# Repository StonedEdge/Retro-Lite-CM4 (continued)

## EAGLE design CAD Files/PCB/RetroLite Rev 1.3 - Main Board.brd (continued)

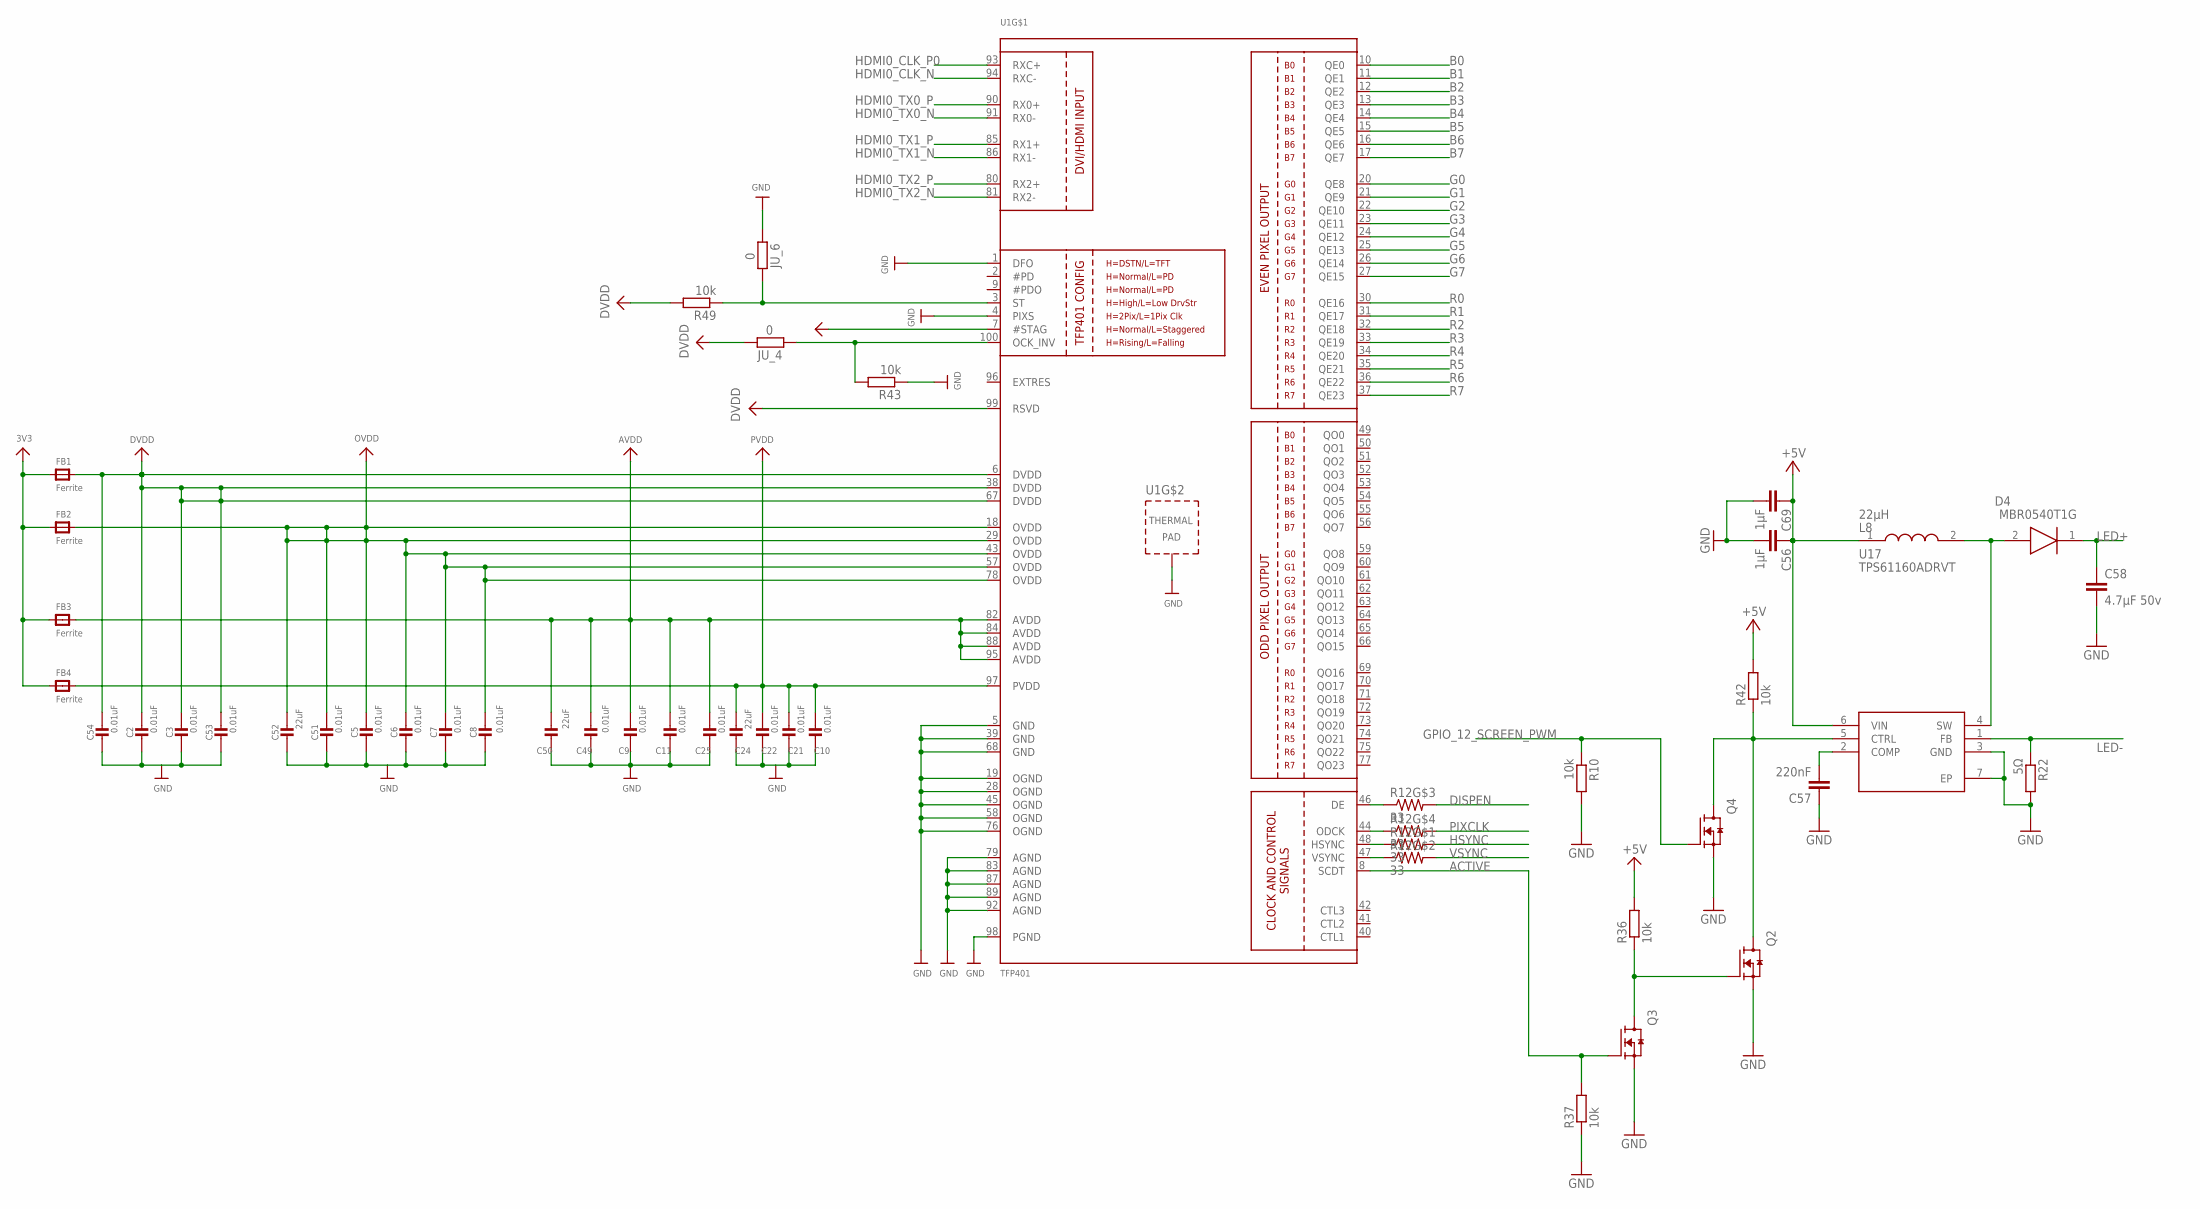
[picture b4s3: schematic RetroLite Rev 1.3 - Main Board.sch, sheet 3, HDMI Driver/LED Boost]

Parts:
C2, C3, C5, C6, C7, C8, C9, C10, C11, C21, C22, C25, C49, C51, C53, C54: 0.01uF; 0603-NO
C24, C50, C52: 22uF; 0603-NO
C56, C69: 1µF; C0603
C57: 220nF; C0603
C58: 4.7µF 50v; C0805
D4: MBR0540T1G; SOD3716X135N
FB1, FB2, FB3, FB4: Ferrite; _0805MP
JU_4, JU_6: 0; R0402
L8: 22µH; VLCF4020_1
Q2, Q3, Q4: AO3400A; SOT95P280X125-3N
R10, R36, R37, R42: 10k; R0603
R12: 33; RESPACK_4X0603
R22: 5Ω; R0603
R43, R49: 10k; R0402
U1: TFP401; S-PQFP-G100
U17: TPS61160ADRVT; SON65P200X200X80-7N

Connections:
3V3: FB1.1, FB2.1, FB3.1, FB4.1; also elsewhere on the board
+5V: C56.1, C69.1, L8.1, R36.2, R42.2, U17.6 (VIN); also elsewhere on the board
ACTIVE: Q3.1 (G), R37.2, U1.8 (SCDT); also elsewhere on the board
ASD: R12.3 (1), U1.46 (DE)
AVDD: C9.1, C11.1, C25.1, C49.1, C50.1, FB3.2, U1.82 (AVDD), U1.84 (AVDD), U1.88 (AVDD), U1.95 (AVDD)
B0: U1.10 (QE0); also elsewhere on the board
B1: U1.11 (QE1); also elsewhere on the board
B2: U1.12 (QE2); also elsewhere on the board
B3: U1.13 (QE3); also elsewhere on the board
B4: U1.14 (QE4); also elsewhere on the board
B5: U1.15 (QE5); also elsewhere on the board
B6: U1.16 (QE6); also elsewhere on the board
B7: U1.17 (QE7); also elsewhere on the board
CVB: R12.2 (1), U1.47 (VSYNC)
DISPEN: R12.6 (2); also elsewhere on the board
DVDD: C2.1, C3.1, C53.1, C54.1, FB1.2, JU_4.2, R49.2, U1.6 (DVDD), U1.7 (#STAG), U1.38 (DVDD), U1.67 (DVDD), U1.99 (RSVD)
G0: U1.20 (QE8); also elsewhere on the board
G1: U1.21 (QE9); also elsewhere on the board
G2: U1.22 (QE10); also elsewhere on the board
G3: U1.23 (QE11); also elsewhere on the board
G4: U1.24 (QE12); also elsewhere on the board
G5: U1.25 (QE13); also elsewhere on the board
G6: U1.26 (QE14); also elsewhere on the board
G7: U1.27 (QE15); also elsewhere on the board
GND: C2.2, C3.2, C5.2, C6.2, C7.2, C8.2, C9.2, C10.2, C11.2, C21.2, C22.2, C24.2, C25.2, C49.2, C50.2, C51.2, C52.2, C53.2, C54.2, C56.2, C57.1, C58.2, C69.2, JU_6.1, Q2.2 (S), Q3.2 (S), Q4.2 (S), R10.2, R22.2, R37.1, R43.1, U1.1 (DFO), U1.4 (PIXS), U1.5 (GND), U1.19 (OGND), U1.28 (OGND), U1.39 (GND), U1.45 (OGND), U1.58 (OGND), U1.68 (GND), U1.76 (OGND), U1.79 (AGND), U1.83 (AGND), U1.87 (AGND), U1.89 (AGND), U1.92 (AGND), U1.98 (PGND), U1.P$1 (TP), U1.P$2 (TP), U1.P$3 (TP), U1.P$4 (TP), U1.P$5 (TP), U1.P$6 (TP), U1.P$7 (TP), U1.P$8 (TP), U1.P$9 (TP), U1.P$10 (TP), U1.P$11 (TP), U1.P$12 (TP), U1.P$13 (TP), U1.P$14 (TP), U1.P$15 (TP), U1.P$16 (TP), U1.THERMAL (TP), U17.3 (GND), U17.7 (EP); also elsewhere on the board
GPIO_12_SCREEN_PWM: Q4.1 (G), R10.1; also elsewhere on the board
HDMI0_CLK_N: U1.94 (RXC-); also elsewhere on the board
HDMI0_CLK_P0: U1.93 (RXC+); also elsewhere on the board
HDMI0_TX0_N: U1.91 (RX0-); also elsewhere on the board
HDMI0_TX0_P: U1.90 (RX0+); also elsewhere on the board
HDMI0_TX1_N: U1.86 (RX1-); also elsewhere on the board
HDMI0_TX1_P: U1.85 (RX1+); also elsewhere on the board
HDMI0_TX2_N: U1.81 (RX2-); also elsewhere on the board
HDMI0_TX2_P: U1.80 (RX2+); also elsewhere on the board
HSYNC: R12.8 (2); also elsewhere on the board
LED+: C58.1, D4.1 (K); also elsewhere on the board
LED-: R22.1, U17.1 (FB); also elsewhere on the board
unnamed: C57.2, U17.2 (COMP)
unnamed: D4.2 (A), L8.2, U17.4 (SW)
unnamed: JU_4.1, R43.2, U1.100 (OCK_INV)
unnamed: Q2.3 (D), Q4.3 (D), R42.1, U17.5 (CTRL)
unnamed: Q2.1 (G), Q3.3 (D), R36.1
NEW: JU_6.2, R49.1, U1.3 (ST)
OVDD: C5.1, C6.1, C7.1, C8.1, C51.1, C52.1, FB2.2, U1.18 (OVDD), U1.29 (OVDD), U1.43 (OVDD), U1.57 (OVDD), U1.78 (OVDD)
PIXCLK: R12.5 (2); also elsewhere on the board
PVDD: C10.1, C21.1, C22.1, C24.1, FB4.2, U1.97 (PVDD)
R0: U1.30 (QE16); also elsewhere on the board
R1: U1.31 (QE17); also elsewhere on the board
R2: U1.32 (QE18); also elsewhere on the board
R3: U1.33 (QE19); also elsewhere on the board
R4: U1.34 (QE20); also elsewhere on the board
R5: U1.35 (QE21); also elsewhere on the board
R6: U1.36 (QE22); also elsewhere on the board
R7: U1.37 (QE23); also elsewhere on the board
VSYNC: R12.7 (2); also elsewhere on the board
XCV: R12.1, U1.48 (HSYNC)
ZXC: R12.4 (1), U1.44 (ODCK)

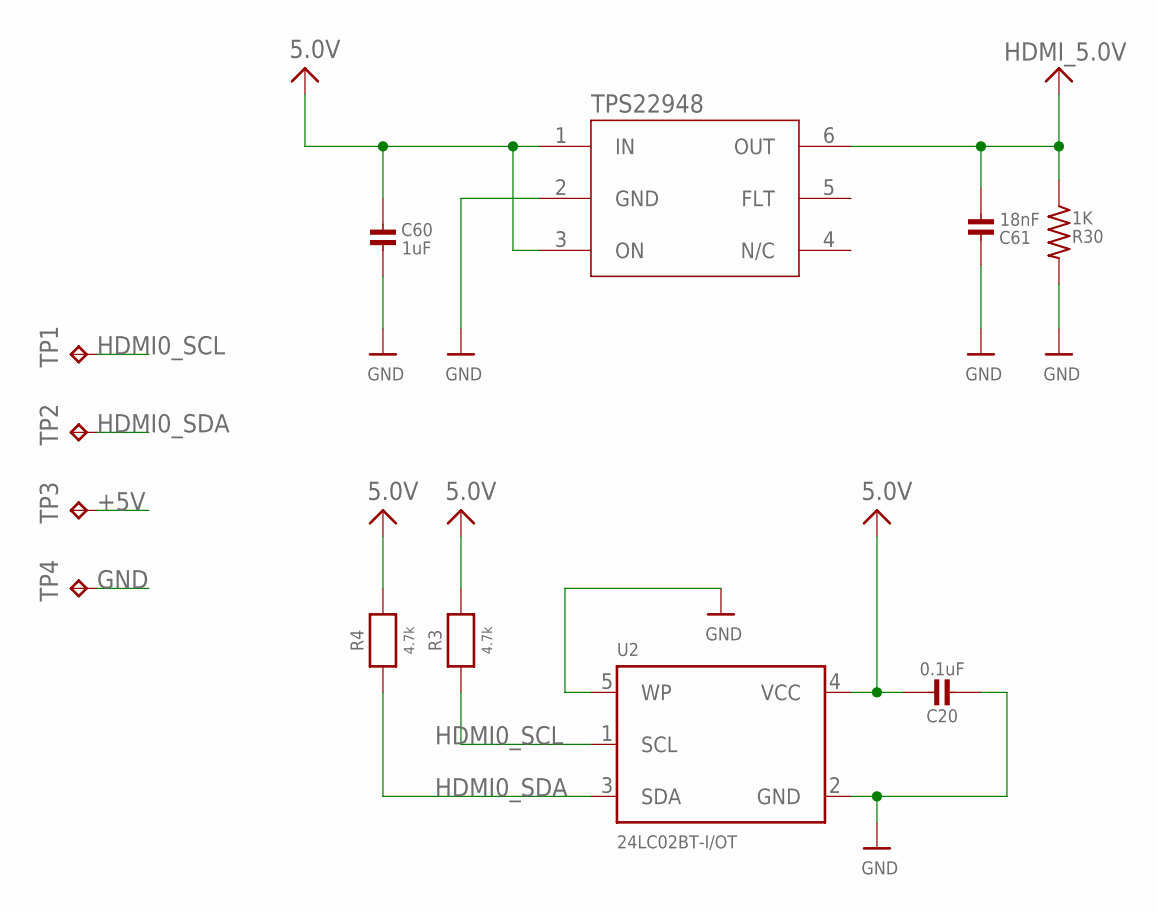
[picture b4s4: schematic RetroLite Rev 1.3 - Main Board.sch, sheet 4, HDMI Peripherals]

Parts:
C20: 0.1uF; 0603-NO
C60: 1uF; 0603-NO
C61: 18nF; 0603-NO
R3, R4: 4.7k; 0603-NO
R30: 1K; R0603
TP1, TP2, TP3, TP4: TPTP07R; TP07R
U2: 24LC02BT-I/OT; SOT23-5
U15: TPS22948; SOT65P210X110-6N

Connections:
+5V: C20.1, C60.1, R3.2, R4.2, TP3.TP, U2.4 (VCC), U15.1 (IN), U15.3 (ON); also elsewhere on the board
GND: C20.2, C60.2, C61.2, R30.2, TP4.TP, U2.2 (GND), U2.5 (WP), U15.2 (GND); also elsewhere on the board
HDMI0_SCL: R3.1, TP1.TP, U2.1 (SCL); also elsewhere on the board
HDMI0_SDA: R4.1, TP2.TP, U2.3 (SDA); also elsewhere on the board
HDMI_5.0V: C61.1, R30.1, U15.6 (OUT); also elsewhere on the board

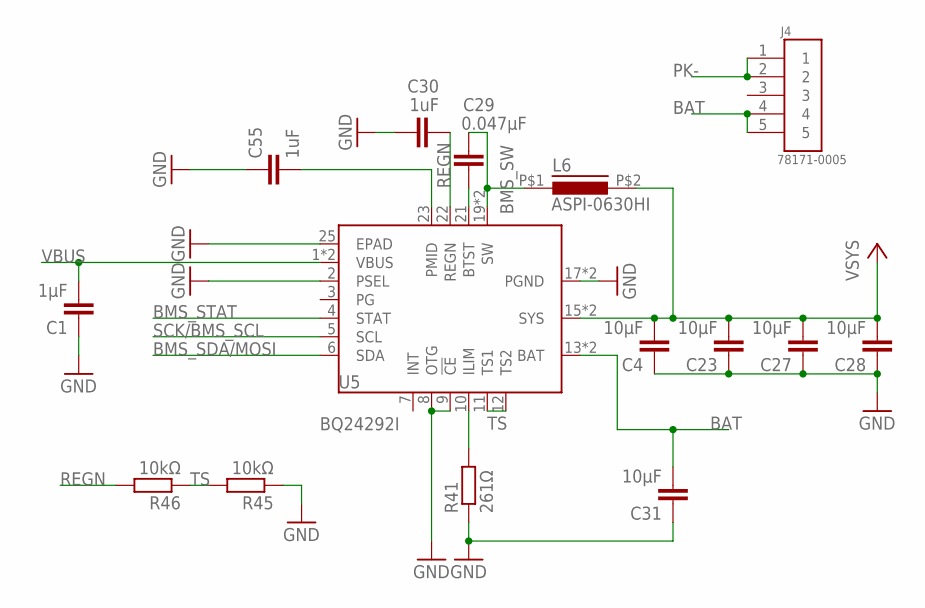
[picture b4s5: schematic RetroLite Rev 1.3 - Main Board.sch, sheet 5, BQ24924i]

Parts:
C1: 1µF; C0805
C4, C23, C27, C28, C31: 10µF; C0805
C29: 0.047µF; C0603
C30, C55: 1uF; C0603
J4: 78171-0005; MOLEX_78171-0005
L6: ASPI-0630HI
R41: 261Ω; R0603
R45, R46: 10kΩ; R0603
U5: BQ24292I; QFN50P400X400X100-25N

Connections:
BAT: C31.2, J4.4, J4.5, U5.13 (BAT), U5.14 (BAT); also elsewhere on the board
BMS_SDA/MOSI: U5.6 (SDA); also elsewhere on the board
BMS_STAT: U5.4 (STAT); also elsewhere on the board
BMS_SW: C29.1, L6.P$1 (1), U5.19 (SW), U5.20 (SW)
GND: C1.1, C4.1, C23.1, C27.1, C28.1, C30.1, C31.1, C55.1, R41.1, R45.1, U5.2 (PSEL), U5.8 (OTG), U5.9 (!CE), U5.17 (PGND), U5.18 (PGND), U5.25 (EPAD); also elsewhere on the board
unnamed: C55.2, U5.23 (PMID)
unnamed: C29.2, U5.21 (BTST)
unnamed: R41.2, U5.10 (ILIM)
PK-: J4.1, J4.2; also elsewhere on the board
REGN: C30.2, R46.2, U5.22 (REGN)
SCK/BMS_SCL: U5.5 (SCL); also elsewhere on the board
TS: R45.2, R46.1, U5.11 (TS1), U5.12 (TS2)
VBUS: C1.2, U5.1 (VBUS), U5.24 (VBUS); also elsewhere on the board
VSYS: C4.2, C23.2, C27.2, C28.2, L6.P$2 (2), U5.15 (SYS), U5.16 (SYS); also elsewhere on the board

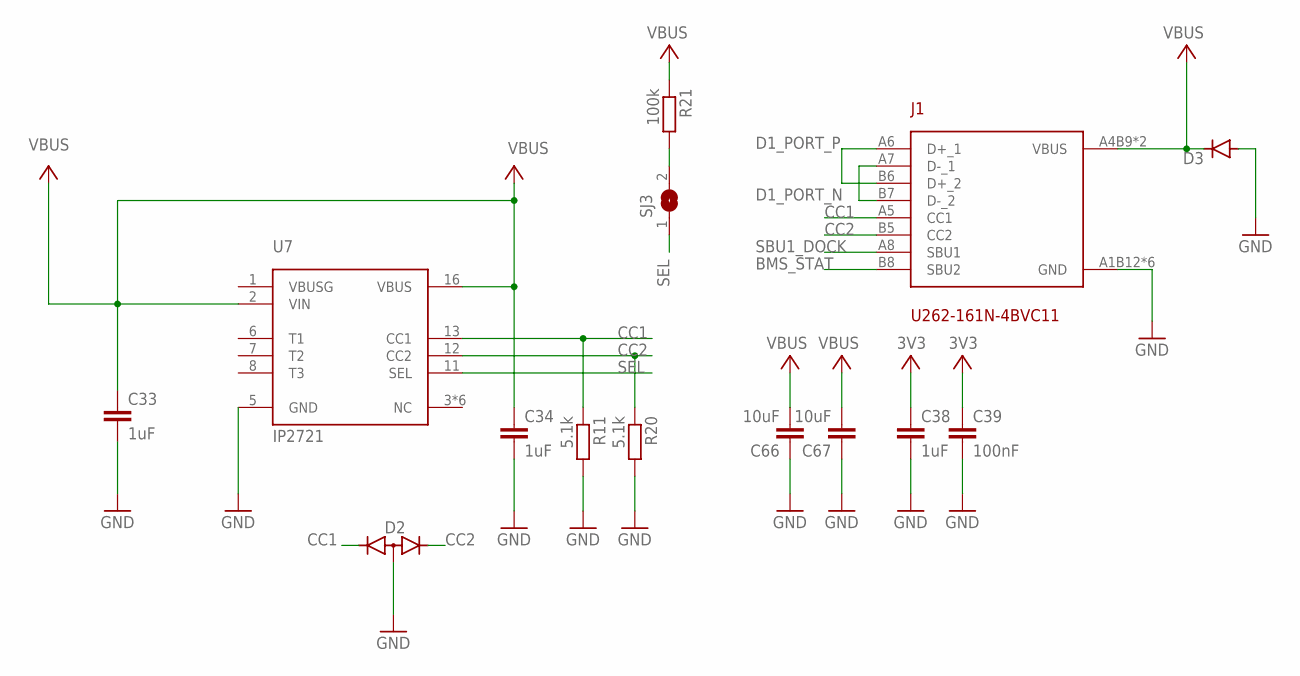
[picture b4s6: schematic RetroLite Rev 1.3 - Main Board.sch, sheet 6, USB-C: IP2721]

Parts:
C33, C34: 1uF; C0805
C38: 1uF; C0603
C39: 100nF; C0603
C66, C67: 10uF; C0805
D2: ESDA25W; SOT65P210X110-3N
D3: ESDA25P35-1U1M; ESDA8P801U1M
J1: U262-161N-4BVC11
R11, R20: 5.1k; R0603
R21: 100k; R0603
SJ3: SOLDERJUMPER; SOLDERJUMPER_ARROW_NOPASTE
U7: IP2721; TSSOP-16

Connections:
3V3: C38.1, C39.1; also elsewhere on the board
BMS_STAT: J1.B8 (SBU2); also elsewhere on the board
CC1: D2.1 (K2), J1.A5 (CC1), R11.1, U7.13 (CC1)
CC2: D2.2 (K1), J1.B5 (CC2), R20.1, U7.12 (CC2)
D1_PORT_N: J1.A7 (D-_1), J1.B7 (D-_2); also elsewhere on the board
D1_PORT_P: J1.A6 (D+_1), J1.B6 (D+_2); also elsewhere on the board
GND: C33.2, C34.2, C38.2, C39.2, C66.1, C67.1, D2.3 (A), D3.1 (A), J1.A1B12 (GND), J1.B1A12 (GND), J1.SHIELD_1 (GND), J1.SHIELD_2 (GND), J1.SHIELD_3 (GND), J1.SHIELD_4 (GND), R11.2, R20.2, U7.5 (GND); also elsewhere on the board
unnamed: R21.2, SJ3.2
SBU1_DOCK: J1.A8 (SBU1); also elsewhere on the board
SEL: SJ3.1, U7.11 (SEL)
VBUS: C33.1, C34.1, C66.2, C67.2, D3.2 (C), J1.A4B9 (VBUS), J1.B4A9 (VBUS), R21.1, U7.2 (VIN), U7.16 (VBUS); also elsewhere on the board

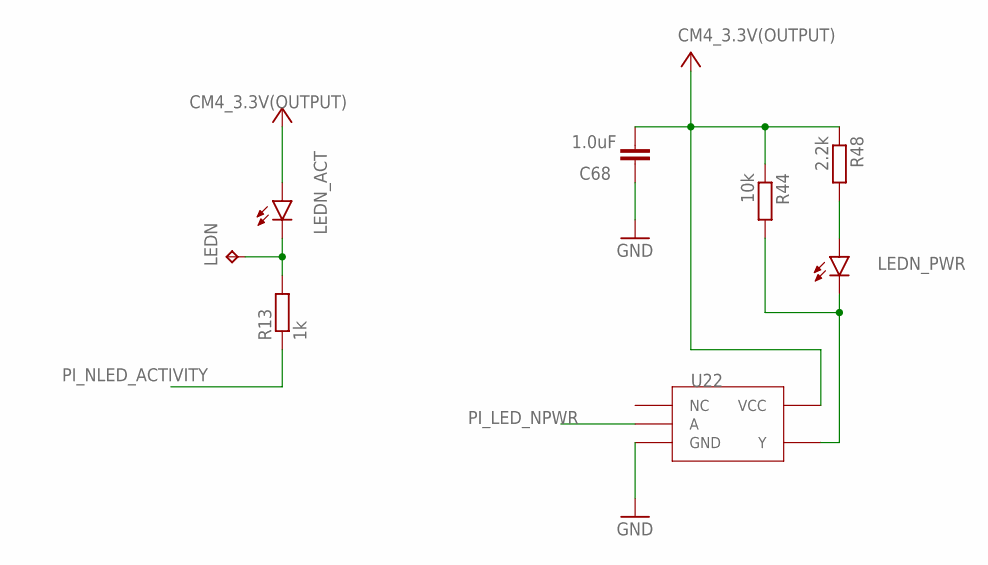
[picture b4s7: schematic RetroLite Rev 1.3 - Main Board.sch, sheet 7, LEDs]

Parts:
C68: 1.0uF; 0603
LEDN: TPTP07R; TP07R
LEDN_ACT: LEDSML0603; SML0603
LEDN_PWR: LEDSML0603; SML0603
R13: 1k; R0603
R44: 10k; R0603
R48: 2.2k; R0603
U22: BUF-74LVC1G07

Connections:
CM4_3.3V(OUTPUT): C68.2, LEDN_ACT.A, R44.1, R48.1, U22.VCC; also elsewhere on the board
GND: C68.1, U22.GND; also elsewhere on the board
unnamed: LEDN.TP, LEDN_ACT.C, R13.2
unnamed: LEDN_PWR.A, R48.2
unnamed: LEDN_PWR.C, R44.2, U22.Y
PI_LED_NPWR: U22.A; also elsewhere on the board
PI_NLED_ACTIVITY: R13.1; also elsewhere on the board

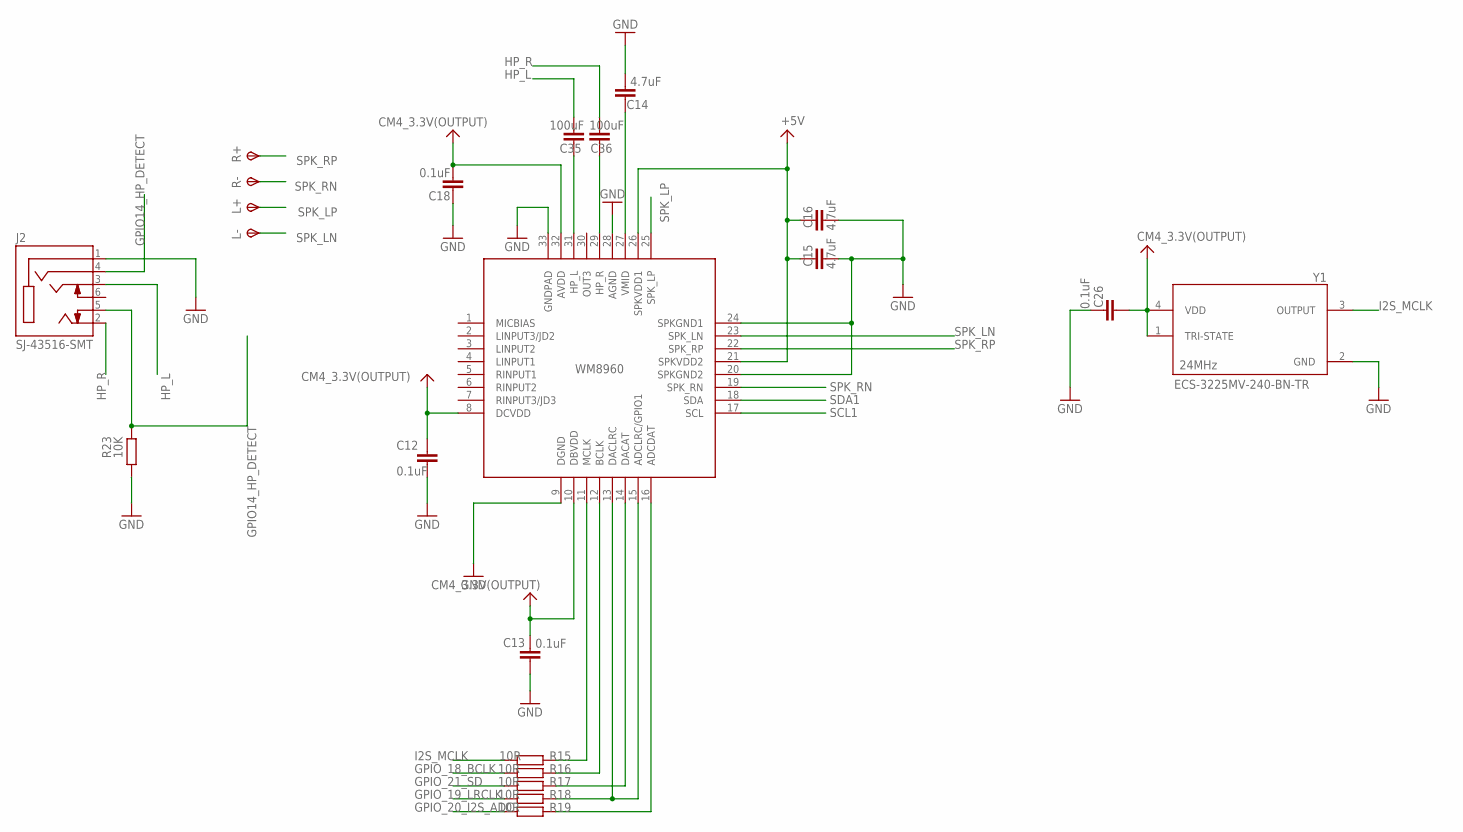
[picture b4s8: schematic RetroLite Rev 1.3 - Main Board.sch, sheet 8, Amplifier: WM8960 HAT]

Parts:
C12, C13, C18, C26: 0.1uF; C0603
C14, C15, C16: 4.7uF; C0603
C35, C36: 100uF; C1206
J2: SJ-43516-SMT; CUI_SJ-43516-SMT
L+: TPSTP09SQ; TP09SQ
L-: TPSTP09SQ; TP09SQ
R15, R16, R17, R18, R19: 10R; R0603
R23: 10K; R0603
R+: TPSTP09SQ; TP09SQ
R-: TPSTP09SQ; TP09SQ
U6: WM8960; QFN50P500X500X100-33N
Y1: ECS-3225MV-240-BN-TR; OSC_ECS-2333-160-BN-TR

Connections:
+5V: C15.1, C16.1, U6.21 (SPKVDD2), U6.26 (SPKVDD1); also elsewhere on the board
ADC: R19.2, U6.16 (ADCDAT)
BCLK: R16.2, U6.12 (BCLK)
CM4_3.3V(OUTPUT): C12.1, C13.1, C18.2, C26.2, U6.8 (DCVDD), U6.10 (DBVDD), U6.32 (AVDD), Y1.1 (TRI-STATE), Y1.4 (VDD); also elsewhere on the board
DAC: R17.2, U6.14 (DACAT)
GND: C12.2, C13.2, C14.2, C15.2, C16.2, C18.1, C26.1, J2.1 (SLEEVE), R23.2, U6.9 (DGND), U6.20 (SPKGND2), U6.24 (SPKGND1), U6.28 (AGND), U6.33 (GNDPAD), Y1.2 (GND); also elsewhere on the board
GPIO14_HP_DETECT: J2.4 (RING2), J2.5 (TIP_SWITCH), R23.1; also elsewhere on the board
GPIO_18_BCLK: R16.1; also elsewhere on the board
GPIO_19_LRCLK: R18.1; also elsewhere on the board
GPIO_20_I2S_ADC: R19.1; also elsewhere on the board
GPIO_21_SD: R17.1; also elsewhere on the board
HP_L: C35.2, J2.3 (RING1)
HP_R: C36.2, J2.2 (TIP)
I2S_MCLK: R15.1, Y1.3 (OUTPUT)
MCLK: R15.2, U6.11 (MCLK)
unnamed: C14.1, U6.27 (VMID)
unnamed: C35.1, U6.31 (HP_L)
unnamed: C36.1, U6.29 (HP_R)
SCL1: U6.17 (SCL); also elsewhere on the board
SDA1: U6.18 (SDA); also elsewhere on the board
SPK_LN: L-.TP, U6.23 (SPK_LN)
SPK_LP: L+.TP, U6.25 (SPK_LP)
SPK_RN: R-.TP, U6.19 (SPK_RN)
SPK_RP: R+.TP, U6.22 (SPK_RP)
WS: R18.2, U6.13 (DACLRC), U6.15 (ADCLRC/GPIO1)

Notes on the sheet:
WM8960
24MHz
0.1uF

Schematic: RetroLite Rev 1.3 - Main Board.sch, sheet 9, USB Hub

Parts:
C40: 1uF; C0603
C45, C48: 18pF; C0603
R25: 12k; 0603
R27, R28, R29, R40: 56k; 0603
U9: USB2422T/MJ; SQFN24_4X4MC_MCH
U10, U12, U13: RCLAMP0582BQTCT; SC75-3L_SEM
Y2: ECS-240-8-36CKM-TR; XTAL_ECS-160-10-36-JGN-TR

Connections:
3V3: U9.1 (VDD33), U9.9 (VDD33), U9.15 (RESET_N), U9.16 (VBUS_DET), U9.18 (VDD33); also elsewhere on the board
D1_PORT_N: U9.4 (USBDN_DN2), U10.2; also elsewhere on the board
D1_PORT_P: U9.5 (USBDP_DN2), U10.1; also elsewhere on the board
D_N: U9.2 (USBDN_DN1), U12.2; also elsewhere on the board
D_P: U9.3 (USBDP_DN1), U12.1; also elsewhere on the board
GND: C40.1, C45.2, C48.2, R25.2, R27.2, R28.2, R40.2, U9.25 (GND), U10.3, U12.3, U13.3, Y2.2 (GND), Y2.4 (GND); also elsewhere on the board
unnamed: R40.1, U9.14 (SMBCLK/CFG_SEL)
unnamed: R25.1, U9.24 (RBIAS)
unnamed: C40.2, U9.10 (CFRILT)
unnamed: R28.1, U9.17 (SUSP_IND/NON_REM0)
unnamed: R27.1, U9.13 (SMBDAT/NON_REM1)
unnamed: C45.1, R29.1, U9.21 (XTALOUT), Y2.1 (IN/OUT)
unnamed: C48.1, R29.2, U9.22 (XTALIN_CLKIN), Y2.3 (OUT/IN)
USB_PI_N: U9.19 (USBDN_UP), U13.2; also elsewhere on the board
USB_PI_P: U9.20 (USBDP_UP), U13.1; also elsewhere on the board

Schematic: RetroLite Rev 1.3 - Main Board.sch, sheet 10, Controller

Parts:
C37: 0.1uF; R0402
LEFTPCB: 1-1734839-4; TE_1-1734839-4
R24: 100K; R0402
RIGHTPCB: 1-1734839-4; TE_1-1734839-4
U4: TS3USB221A; QFN-10-RSE

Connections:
3V3: C37.2, U4.10 (VCC); also elsewhere on the board
+5V: LEFTPCB.1, RIGHTPCB.14; also elsewhere on the board
A2: LEFTPCB.5, RIGHTPCB.10
A3: LEFTPCB.6, RIGHTPCB.9
D1_PORT_N: U4.4 (2D-); also elsewhere on the board
D1_PORT_P: U4.3 (2D+); also elsewhere on the board
D8: LEFTPCB.7, RIGHTPCB.8
D9: LEFTPCB.8, RIGHTPCB.7
D10: LEFTPCB.9, RIGHTPCB.6
D11: LEFTPCB.10, RIGHTPCB.5
D12: LEFTPCB.11, RIGHTPCB.4
D13: LEFTPCB.12, RIGHTPCB.3
D15: LEFTPCB.13, RIGHTPCB.2
D16: LEFTPCB.14, RIGHTPCB.1
D_N: RIGHTPCB.13, U4.2 (1D-); also elsewhere on the board
D_P: RIGHTPCB.12, U4.1 (1D+); also elsewhere on the board
GND: C37.1, LEFTPCB.4, LEFTPCB.P1 (S), LEFTPCB.P2 (S), R24.2, RIGHTPCB.11, RIGHTPCB.P1 (S), RIGHTPCB.P2 (S), U4.5 (VSS), U4.6 (!OE); also elsewhere on the board
SBU1_DOCK: R24.1, U4.9 (S); also elsewhere on the board
USB_PI_N: U4.7 (D-); also elsewhere on the board
USB_PI_P: U4.8 (D+); also elsewhere on the board

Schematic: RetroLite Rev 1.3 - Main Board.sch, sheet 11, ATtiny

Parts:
C17, C19, C62: 0.1uF; C0603
J6: 0781710004; MOLEX_0781710004
JU_2, JU_3, JU_5: 0; R0402
R5, R32, R33: 4.7k; R0603
R31, R34, R56: 10k; R0603
R54: 1k; R0603
R55: 15k; R0603
U14: MCU-ATTINY84A-MU(QFN20); QFN20G-0.5-4X4MM
U19, U20: SN74LVC1G17DCKR; SOT65P210X110-5N
U$29: 1MM_PIC_PROGRAMING_HEADER; 1MM_PIC-PROGRAMING_HEADER

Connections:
+5V: R34.1; also elsewhere on the board
BMS_SDA/MOSI: R32.2, U14.16 (PA6(ADC6/DI/MOSI/SDA/OC1A/PCINT6)), U$29.4; also elsewhere on the board
BMS_STAT: R34.2, R54.1; also elsewhere on the board
CM4_3.3V(OUTPUT): C17.1, R56.2, U20.5 (VCC); also elsewhere on the board
EN: R31.2, U14.4 (PA1(ADC1/AIN0/PCINT1)); also elsewhere on the board
GLOBAL_EN: JU_2.1, JU_2.2, U14.15 (PA7(ADC7/OC0B/ICP/PCINT7)); also elsewhere on the board
GND: C17.2, C19.1, C62.1, J6.4, J6.S1 (SHIELD), J6.S2 (SHIELD), R31.1, R55.2, R56.1, U14.8 (GND), U14.PAD, U19.3 (GND), U20.3 (GND), U$29.2; also elsewhere on the board
GPIO4_BMS_STAT: R54.2, R55.1; also elsewhere on the board
GPIO15_V-: J6.3; also elsewhere on the board
GPIO16_VOLTAGE_SHUTDOWN: U19.2 (A); also elsewhere on the board
GPIO16_VOLTAGE_SHUTDOWN_ATTINY: U14.5 (PA0(ADC0/AREF/PCINT0)), U19.4 (Y)
GPIO24_V+: J6.2; also elsewhere on the board
GPIO25_PI_SHUTDOWN_INIT: JU_5.2; also elsewhere on the board
GPIO25_PI_SHUTDOWN_INIT_ATTINY: U14.3 (PA2(ADC2/AIN1/PCINT2)), U20.2 (A)
GPIO25_PI_SHUTDOWN_INIT_JUP: JU_5.1, U20.4 (Y)
MISO: U14.20 (PA5(ADC5/DO/MISO/OC1B/PCINT5), U$29.5
PWR_BUTTON: J6.1, U14.14 (PB2(PCINT10/INT0/OC0A/CLKOUT))
RESET: R5.2, U14.13 (PB3(PCINT11/DW/!RESET)), U$29.6
RUN_PG: JU_3.1, JU_3.2, U14.2 (PA3(ADC3/T0/PCINT3)); also elsewhere on the board
SCK/BMS_SCL: R33.2, U14.1 (PA4(ADC4/USCK/SCL/T1/PCINT4)), U$29.3; also elsewhere on the board
VSYS: C19.2, C62.2, R5.1, R32.1, R33.1, U14.9 (VCC), U19.5 (VCC), U$29.1; also elsewhere on the board

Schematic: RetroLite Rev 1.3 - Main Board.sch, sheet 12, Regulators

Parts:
C32, C63: 1uF; 0603-NO
C41, C42, C43, C44, C47: 1.0uF; 0603
C46: 10uF; 0805
R26: 510K; R0603
R35: 162K; R0603
U8: TPS61230DRCT; SON50P300X300X100-11N
U16: TPS82085; SON65P280X300X133-9N
U18: INDUCTOR_SMALL

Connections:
3V3: C32.1, C47.2, C63.1, R26.2, U16.8 (VOUT); also elsewhere on the board
+5V: C41.1, C42.1, C43.1, U8.3 (VOUT), U8.4 (COUT), U8.7 (FB); also elsewhere on the board
CM4_3.3V(OUTPUT): U16.1 (EN); also elsewhere on the board
EN: U8.9 (EN); also elsewhere on the board
GND: C32.2, C41.2, C42.2, C43.2, C44.1, C46.1, C47.1, C63.2, R35.1, U8.11 (GND), U16.5 (GND), U16.6 (GND), U16.9 (GND), U16.P$1 (GND), U16.P$2 (GND), U16.P$3 (GND); also elsewhere on the board
unnamed: U8.1 (SW_1), U8.2 (SW_2), U18.1
unnamed: R26.1, R35.2, U16.7 (FB)
VSYS: C44.2, C46.2, U8.10 (VIN), U16.3 (VIN), U16.4 (VIN), U18.2; also elsewhere on the board

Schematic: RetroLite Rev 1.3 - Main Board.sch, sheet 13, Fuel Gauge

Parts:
C64: 0.47uF; C0402
C65: 0.1uF; C0402
R38, R47, R53: 4.7k; R0603
R39: PS0306DRF7T0R01L
U11: MAX17055ETB+T; 21-100013A_T102A2+1C_MXM

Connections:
BAT: C65.1, U11.10 (BATT); also elsewhere on the board
CM4_3.3V(OUTPUT): R38.1, R47.1, R53.1; also elsewhere on the board
GND: R39.1; also elsewhere on the board
GPIO17_INT: R53.2, U11.8 (ALRT); also elsewhere on the board
unnamed: C64.1, U11.7 (REG)
unnamed: R39.2, U11.5 (CSN)
unnamed: R39.3, U11.2 (AIN), U11.6 (CSP), U11.11 (EPAD)
PK-: C64.2, C65.2, R39.4; also elsewhere on the board
SCL1: R47.2, U11.3 (SCL); also elsewhere on the board
SDA1: R38.2, U11.4 (SDA); also elsewhere on the board

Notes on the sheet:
R39
0.01Ω

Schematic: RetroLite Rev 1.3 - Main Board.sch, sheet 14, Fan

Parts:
D1: BAS70; SOT23
J3: 2026560021; CONN_2026560021_MOL
Q1: AO3400A; SOT95P280X125-3N
R52: 10k; R0603

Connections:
+5V: D1.3 (C), J3.1; also elsewhere on the board
GND: Q1.2 (S), R52.1; also elsewhere on the board
GPIO13_PI_FAN: Q1.1 (G), R52.2; also elsewhere on the board
unnamed: D1.1 (A), J3.2, Q1.3 (D)
